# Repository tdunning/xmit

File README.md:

# XMIT - New tools for old jobs

This repository has design files and (soon) code for a direct synthesis digital 
mode transmitter optimized for use on amateur bands. It should work well up to 
2m. The novelty here relative to other systems like the [QDX](https://qrp-labs.com/qdx.html)
lies in a few areas:

a) the use of [74LVC2G157](https://www.ti.com/lit/ds/symlink/sn74lvc2g157.pdf) to generate differential drive for a differential
driver such as the [THS6232](https://www.ti.com/lit/ds/symlink/ths6232.pdf) which can
directly drive most balanced antennas without a balun at up to about 5W. This design
avoids the need for fancy gate drive or paralleling FETs in favor of SMT packaging everywhere. 

b) the use of SMT inductors and SMT analog switches such as the 
[74lvc2g53](https://www.ti.com/lit/ds/symlink/sn74lvc2g53.pdf) or 
[74lvc1g66](https://www.ti.com/lit/ds/symlink/sn74lvc1g66.pdf).
This change is not earth-shattering, but it allows a much tighter all-SMT design with as much as 80dB suppression of harmonics.
The high degree of suppression is achieved by using a filter tuned to put the response zeros directly on the harmonics
and careful filter layout to suppress parasitic coupling.

# Transmit filtering

The design of the transmit chain uses one of a number of filters to
reject harmonics of the main frequency. One of these filters is
selected using analog switches to suit the desire transmission
frequency. These filters are designed to have minimal attenuation in
each of several amateur bands. Since these bands are relatively
narrow, passband flatness is not a grave concern. The zeros of the
filters are positioned near the second or third harmonics of the
carrier to suppress these frequencies very strongly. Higher harmonics
have nearly 75dB of suppression.

The response curves for the filters designed so far are shown below.

[Filter response curves](images/filters.png)

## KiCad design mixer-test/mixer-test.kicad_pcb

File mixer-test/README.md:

# Mixer Comparisons

This directory contains design files for PC boards intended to help compare different kinds of mixers, particularly in the HF to VHF regime. 

## The basics

This board has inputs for RF, local oscillator and and baseband outputs (if available). The local oscillator is assumed to be at 3.3V logic levels and is locally buffered to get a differential drive. Test points are available for internal signals.

## The contestants

The mixers available include the LT5560 and Tayloe mixers constructed using SN74CBT3253DR (similar to the FST3253), SN74LVC1G3157, or 74LVC1G66 analog switch. In all cases it is assumed that the desired output is limited to <100kHz. There is no presumption about the frequency of the RF or LO inputs other than they should be near enough to produce a useful baseband output.

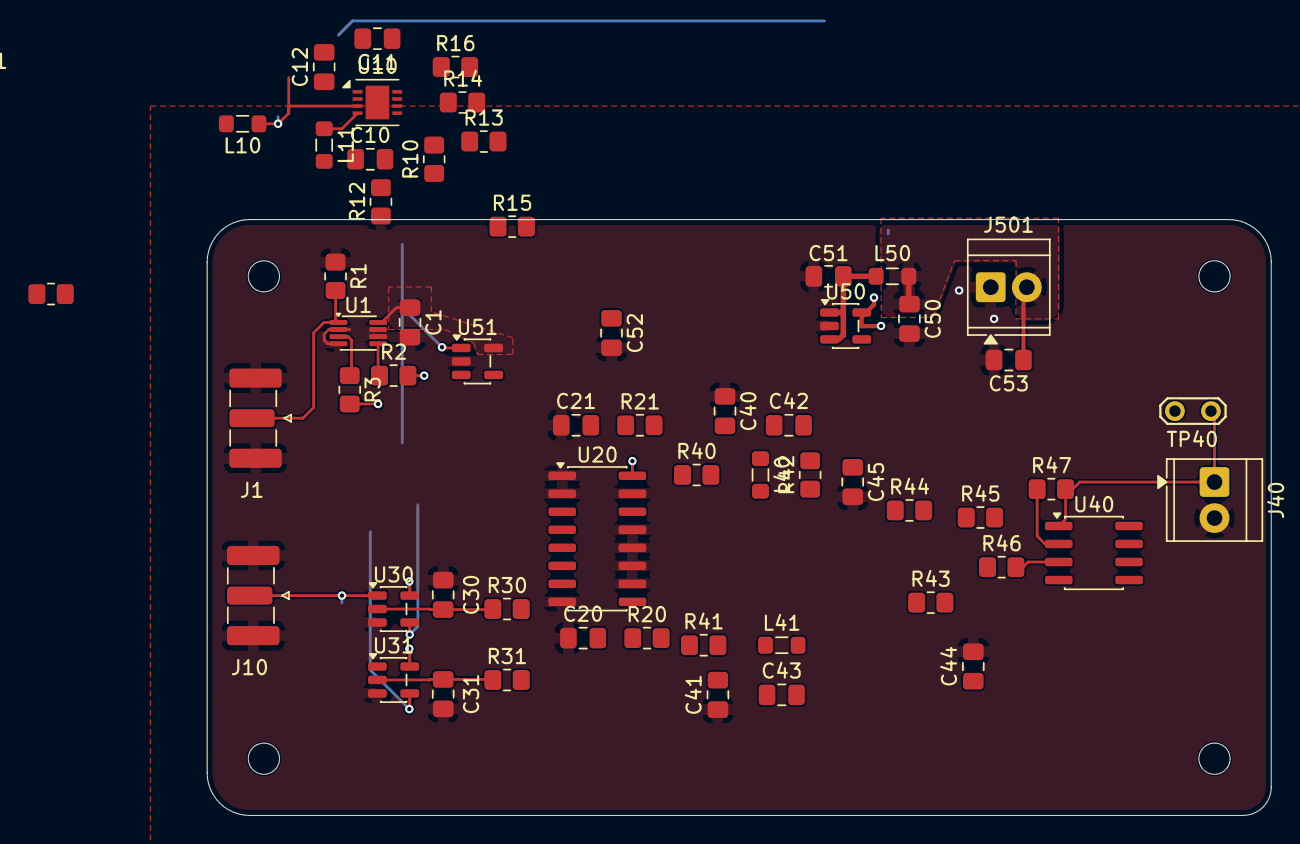
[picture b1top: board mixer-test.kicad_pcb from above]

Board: 4 copper layers, 75.0 x 42.0 mm, 62 parts (0 on the bottom side), 32 nets.

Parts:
C1, C12, C50, C51, C52, C53: 1µF; C_0805_2012Metric_Pad1.18x1.45mm_HandSolder
C10, C11: 220pF; C_0805_2012Metric_Pad1.18x1.45mm_HandSolder
C20, C21, C30, C31: 33pF; C_0805_2012Metric_Pad1.18x1.45mm_HandSolder
C40, C41, C44, C45: 1nF; C_0805_2012Metric_Pad1.18x1.45mm_HandSolder
C42, C43: 47pF; C_0805_2012Metric_Pad1.18x1.45mm_HandSolder
H501, H502, H503, H504: MountingHole_2.2mm_M2
J1, J10: SMA; SMA_Samtec_SMA-J-P-H-ST-EM1_EdgeMount
J40: Conn_01x02_Pin; TerminalBlock_TE_282834-2_1x02_P2.54mm_Horizontal
J501: TerminalBlock_TE_282834-2_1x02_P2.54mm_Horizontal
L10, L11: 100nH; L_0805_2012Metric_Pad1.05x1.20mm_HandSolder
L40, L41: 4.7µH; L_0805_2012Metric_Pad1.05x1.20mm_HandSolder
L50: 1 µH; L_0805_2012Metric_Pad1.05x1.20mm_HandSolder
R1, R10, R12: 100R; R_0805_2012Metric_Pad1.20x1.40mm_HandSolder
R2, R3, R11: 50R; R_0805_2012Metric_Pad1.20x1.40mm_HandSolder
R13, R14: 330R; R_0805_2012Metric_Pad1.20x1.40mm_HandSolder
R15, R16, R20, R21, R30, R31: 0R; R_0805_2012Metric_Pad1.20x1.40mm_HandSolder
R40, R41: 1k; R_0805_2012Metric_Pad1.20x1.40mm_HandSolder
R42, R43: 10R; R_0805_2012Metric_Pad1.20x1.40mm_HandSolder
R44, R45, R46, R47: 10k; R_0805_2012Metric_Pad1.20x1.40mm_HandSolder
TP40: Output; TestPoint_2Pads_Pitch2.54mm_Drill0.8mm
U1: 74LVC2G157; VSSOP-8_2.3x2mm_P0.5mm
U10: LT5560; DFN-8-1EP_3x3mm_P0.5mm_EP1.66x2.38mm
U20: SN74CBT3253; SOIC-16_3.9x9.9mm_P1.27mm
U30, U31: 74LVC1G66; SOT-23-5
U40: OPA2356AIDR; SOIC-8_3.9x4.9mm_P1.27mm
U50: TPS7A2042PDBVRG4; SOT-23-5
U51: TPS7A2033PDBVRG4; SOT-23-5

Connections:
GND: C1.2, C12.2, C20.1, C21.1, C30.1, C31.1, C40.1, C41.1, C44.2, C45.2, C50.2, C51.2, C52.2, C53.2, J1.2 (Ext), J10.2 (Ext), J40.2, J501.1, L10.2, L11.2, R1.1, R10.1, R11.1, R12.1, U1.2 (B), U1.4 (GND), U1.6 (~A/B), U1.7 (~G), U10.9 (PGND), U20.1 (1~OE), U20.2 (S1), U20.8 (GND), U20.10 (2B1), U20.11 (2B2), U20.12 (2B3), U20.13 (2B4), U20.15 (2~OE), U30.3 (GND), U31.3 (GND), U50.2 (GND), U51.2 (GND)
LO: C11.1, R2.2, R10.2, U20.14 (S0), U30.4
unnamed: C30.2, R30.1, U30.2
unnamed: C31.2, R31.1, U31.2
unnamed: C40.2, C42.1, L40.1, R40.2
unnamed: C41.2, C43.1, L41.1, R41.2
unnamed: C42.2, C45.1, R42.2, R44.1
unnamed: C43.2, C44.1, R43.2, R45.1
unnamed: J1.1 (In), R1.2, U1.1 (A)
unnamed: L40.2, R42.1
unnamed: L41.2, R43.1
unnamed: R2.1, U1.5 (Y)
unnamed: R3.1, U1.3 (~Y)
unnamed: L11.1, U10.4 (IN-)
unnamed: C10.2, U10.8 (LO+)
unnamed: C11.2, U10.1 (LO-)
unnamed: R13.2, R15.1, U10.6 (OUT+)
unnamed: R14.2, R16.1, U10.5 (OUT-)
unnamed: C20.2, R20.1, U20.6 (1B1)
unnamed: C21.2, R21.1, U20.5 (1B2)
unnamed: R44.2, R46.2, U40.3 (+)
unnamed: R45.2, R47.1, U40.2 (-)
unnamed: C51.1, L50.2, U50.1 (VIN), U50.3 (EN)
OUT+: R15.2, R20.2, R30.2, R41.1
OUT-: R16.2, R21.2, R31.2, R40.1
OUTPUT: J40.1, R47.2, TP40.1 (1_1), U40.1
RF: J10.1 (In), L10.1, R11.2, U10.3 (IN+), U20.7 (1A), U30.1, U31.1
VCC: C50.1, C53.1, J501.2, L50.1, U51.1 (VIN), U51.3 (EN)
V_amp: R13.1, R14.1
V_drive: C1.1, U1.8 (VCC), U51.5 (VOUT)
V_mix: C12.1, C52.1, U10.2 (EN), U10.7 (VCC), U20.16 (VCC), U30.5 (VCC), U31.5 (VCC), U50.5 (VOUT)
~LO: C10.1, R3.2, R12.2, U31.4

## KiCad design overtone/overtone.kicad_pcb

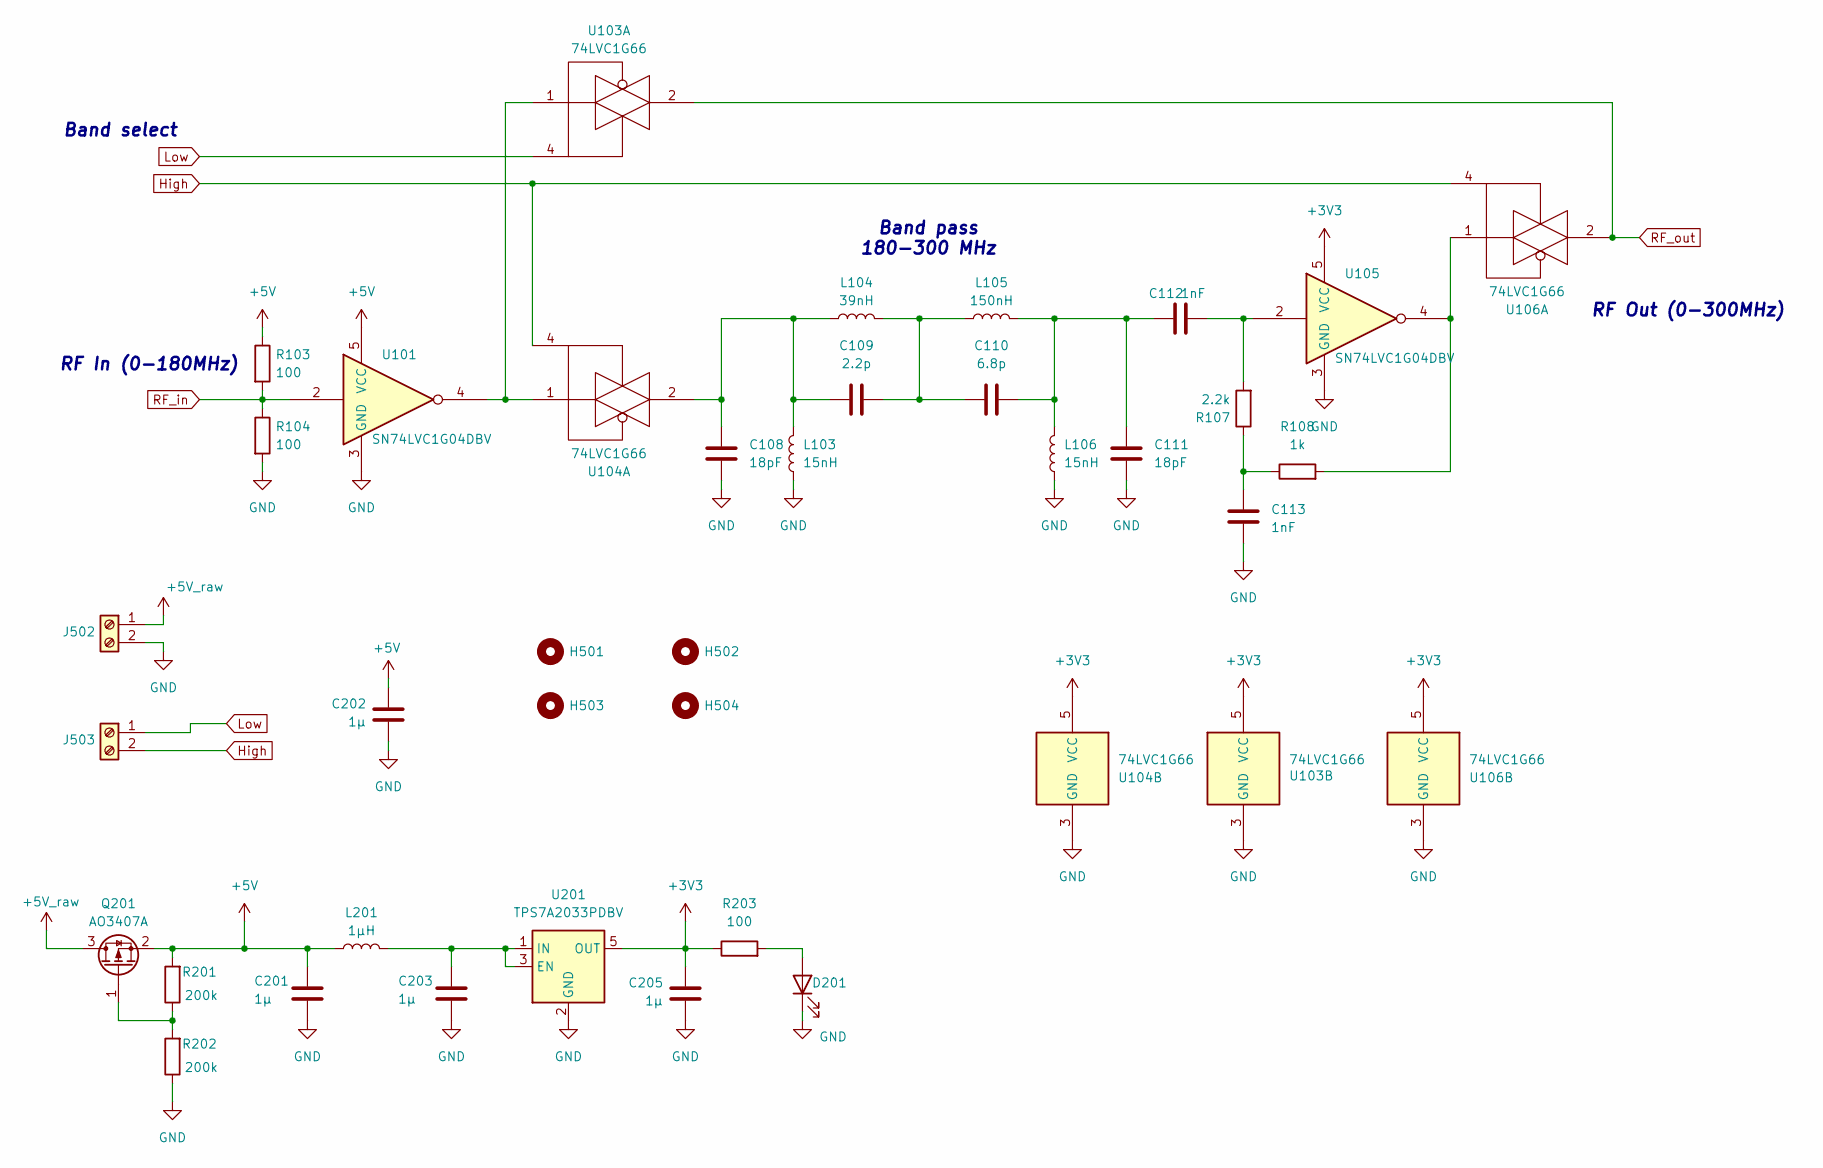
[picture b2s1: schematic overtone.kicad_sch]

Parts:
C108, C111: 18pF; C_0805_2012Metric_Pad1.18x1.45mm_HandSolder; LCSC Part # C519933
C109: 2.2p; C_0805_2012Metric_Pad1.18x1.45mm_HandSolder; LCSC Part # C519933
C110: 6.8p; C_0805_2012Metric_Pad1.18x1.45mm_HandSolder; LCSC Part # C76626
C112: 1nF; C_0805_2012Metric_Pad1.18x1.45mm_HandSolder
C113: 1nF; C_0805_2012Metric_Pad1.18x1.45mm_HandSolder; LCSC Part # C519933
C201, C202, C203, C205: 1µ; C_0805_2012Metric; LCSC Part # C76645
D201: LED; LED_0603_1608Metric; LCSC Part # C12065
H501, H502, H503, H504: MountingHole_2.2mm_M2
J502, J503: TerminalBlock_TE_282834-2_1x02_P2.54mm_Horizontal
L103, L106: 15nH; L_0805_2012Metric_Pad1.05x1.20mm_HandSolder; LCSC Part # C98996
L104: 39nH; L_0805_2012Metric_Pad1.05x1.20mm_HandSolder; LCSC Part # C98996
L105: 150nH; L_0805_2012Metric_Pad1.05x1.20mm_HandSolder; LCSC Part # C98996
L201: 1µH; L_0805_2012Metric_Pad1.05x1.20mm_HandSolder; LCSC Part # C19533
Q201: AO3407A; SOT-23; LCSC Part # C15155
R103: 100; R_0805_2012Metric_Pad1.20x1.40mm_HandSolder; LCSC Part # C114567
R104: 100; R_0805_2012Metric_Pad1.20x1.40mm_HandSolder; LCSC Part # C17378
R107: 2.2k; R_0805_2012Metric_Pad1.20x1.40mm_HandSolder; LCSC Part # C17378
R108: 1k; R_0805_2012Metric_Pad1.20x1.40mm_HandSolder
R201, R202: 200k; R_0805_2012Metric_Pad1.20x1.40mm_HandSolder; LCSC Part # C17539
R203: 100; R_0603_1608Metric; LCSC Part # C22775
U101, U105: SN74LVC1G04DBV; SOT-23-5; LCSC Part # C45367201
U103, U104, U106: 74LVC1G66; SOT-23-5; LCSC Part # C113518
U201: TPS7A2033PDBV; SOT-23-5; LCSC Part # C7827

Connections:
+3V3: C205.2, R203.1, U103.5 (VCC), U104.5 (VCC), U105.5 (VCC), U106.5 (VCC), U201.5 (OUT)
+5V: C201.2, C202.2, L201.1, Q201.2 (S), R103.1, R201.2, U101.5 (VCC)
+5V_raw: J502.1, Q201.3 (D)
GND: C108.1, C111.1, C113.1, C201.1, C202.1, C203.1, C205.1, D201.1 (K), J502.2, L103.1, L106.1, R104.2, R202.1, U101.3 (GND), U103.3 (GND), U104.3 (GND), U105.3 (GND), U106.3 (GND), U201.2 (GND); also elsewhere on the board
High: J503.2, U104.4, U106.4
Low: J503.1, U103.4
unnamed: C108.2, C109.1, L103.2, L104.1, U104.2
unnamed: C109.2, C110.1, L104.2, L105.1
unnamed: C110.2, C111.2, C112.1, L105.2, L106.2
unnamed: C112.2, R107.2, U105.2
unnamed: C113.2, R107.1, R108.1
unnamed: D201.2 (A), R203.2
unnamed: Q201.1 (G), R201.1, R202.2
unnamed: R108.2, U105.4, U106.1
unnamed: U101.4, U103.1, U104.1
unnamed: C203.2, L201.2, U201.1 (IN), U201.3 (EN)
RF_in: R103.2, R104.1, U101.2; also elsewhere on the board
RF_out: U103.2, U106.2

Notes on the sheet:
Band select
RF In (0-180MHz)
RF Out (0-300MHz)
Band pass 180-300 MHz

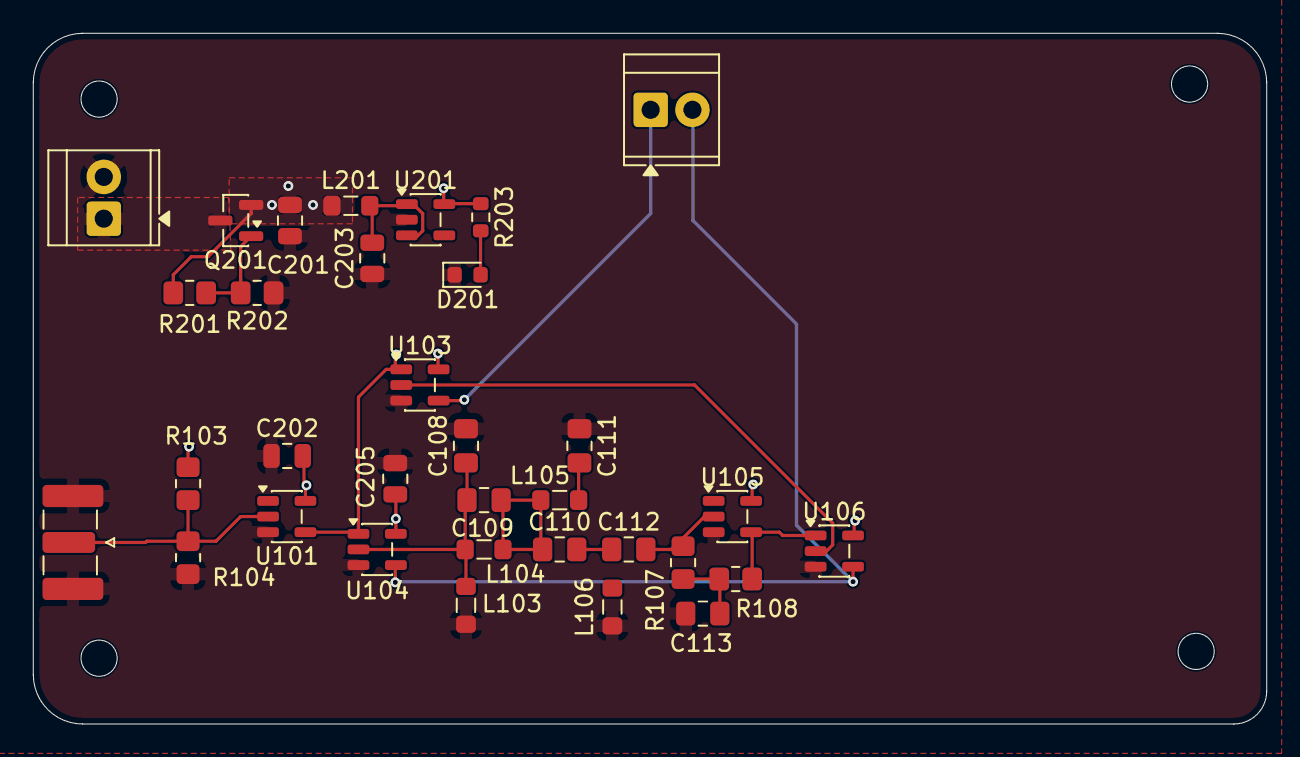
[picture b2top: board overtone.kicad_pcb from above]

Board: 4 copper layers, 75.0 x 42.0 mm, 37 parts (0 on the bottom side), 18 nets.

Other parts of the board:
J506: SMA_Samtec_SMA-J-P-H-ST-EM1_EdgeMount

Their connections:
GND: J506.2 (Ext); also elsewhere on the board
RF_in: J506.1 (In); also elsewhere on the board

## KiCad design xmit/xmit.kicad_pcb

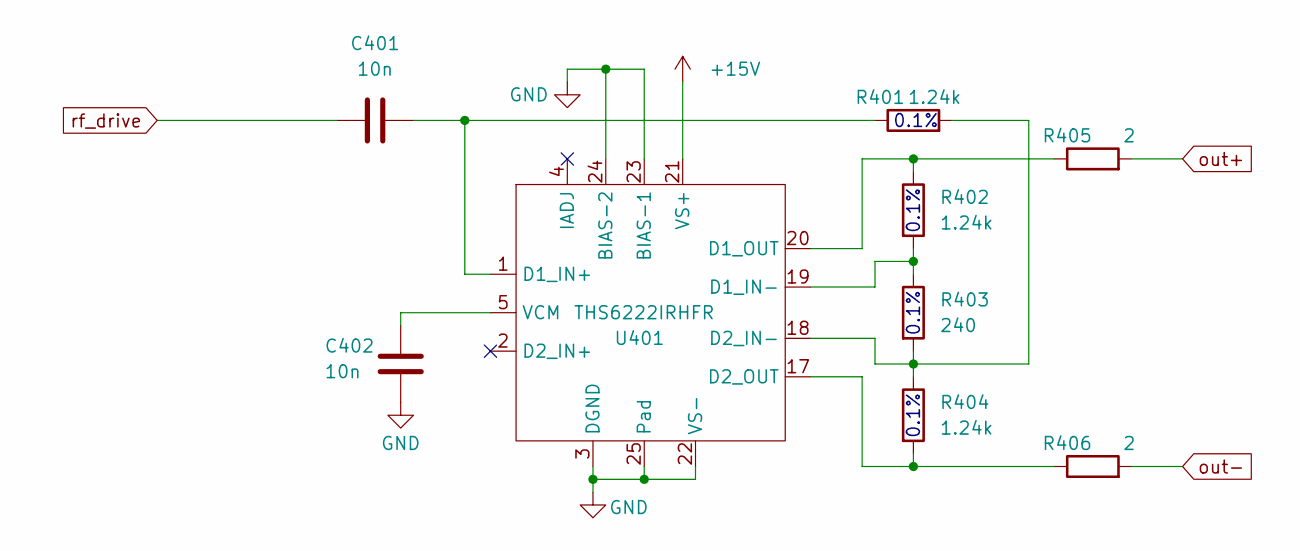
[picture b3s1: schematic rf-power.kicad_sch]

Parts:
C401, C402: 10n; C_0805_2012Metric_Pad1.18x1.45mm_HandSolder; LCSC Part # C76626
R401, R402, R404: 1.24k; R_0402_1005Metric; LCSC Part # C852604
R403: 240; R_0402_1005Metric; LCSC Part # C17572
R405, R406: 2; R_0805_2012Metric_Pad1.20x1.40mm_HandSolder; LCSC Part # C101983
U401: THS6222IRHFR; QFN-24-1EP_4x5mm_P0.5mm_EP2.65x3.65mm_ThermalVias; LCSC Part # C1855812

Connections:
+15V: U401.21 (VS+); also elsewhere on the board
GND: C402.1, U401.3 (DGND), U401.22 (VS-), U401.23 (BIAS-1), U401.24 (BIAS-2), U401.25 (Pad); also elsewhere on the board
unnamed: C401.2, R401.1, U401.1 (D1_IN+)
unnamed: R402.2, R403.1, U401.19 (D1_IN-)
unnamed: R402.1, R405.1, U401.20 (D1_OUT)
unnamed: R401.2, R403.2, R404.1, U401.18 (D2_IN-)
unnamed: R404.2, R406.1, U401.17 (D2_OUT)
unnamed: C402.2, U401.5 (VCM)
out+: R405.2; also elsewhere on the board
out-: R406.2; also elsewhere on the board
rf_drive: C401.1; also elsewhere on the board

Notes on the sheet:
0.1%

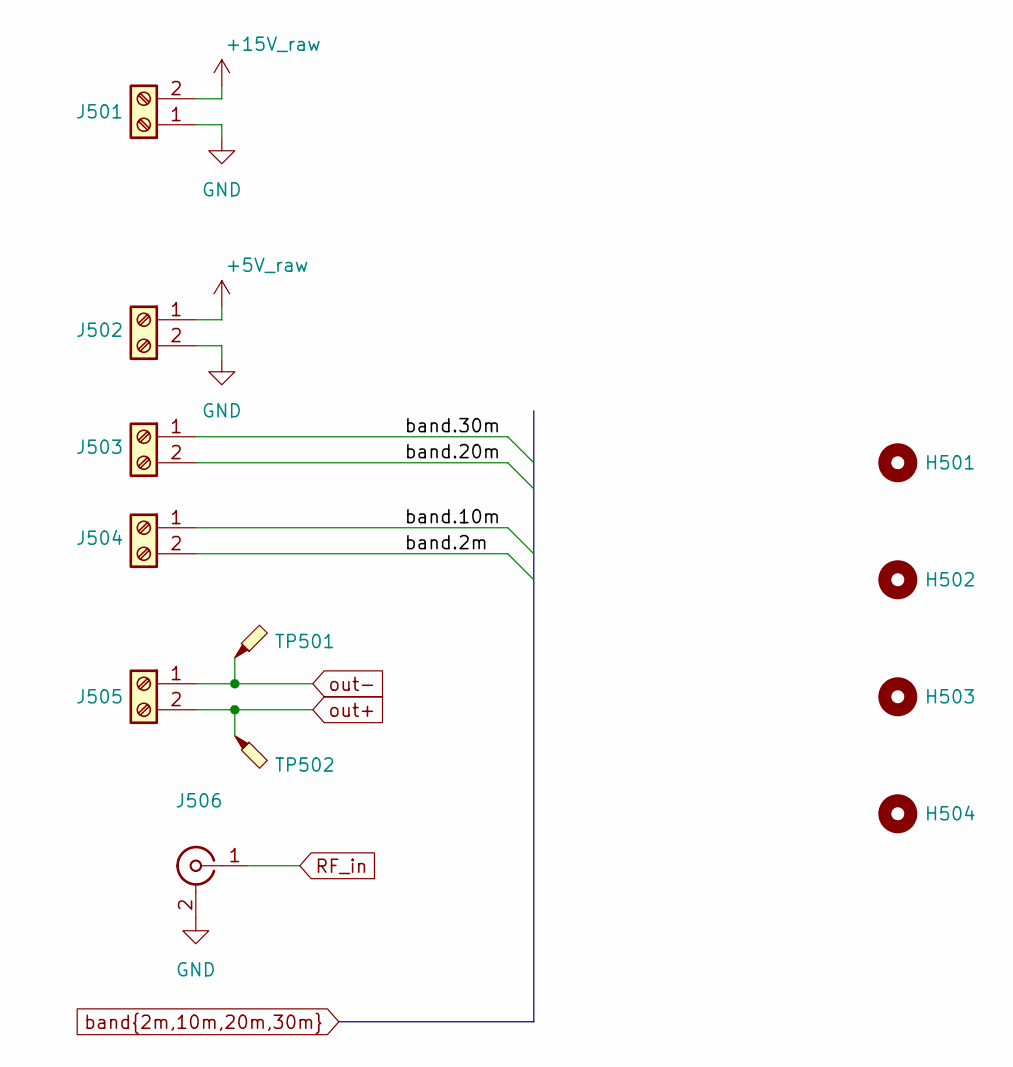
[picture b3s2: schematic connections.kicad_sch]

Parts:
H501, H502, H503, H504: MountingHole_2.2mm_M2
J501, J502, J503, J504, J505: TerminalBlock_TE_282834-2_1x02_P2.54mm_Horizontal
J506: SMA_Samtec_SMA-J-P-H-ST-EM1_EdgeMount; LCSC Part # C49118400
TP501: TestPoint_2Pads_Pitch2.54mm_Drill0.8mm; LCSC Part # C45367201
TP502: TestPoint_2Pads_Pitch2.54mm_Drill0.8mm; LCSC Part # C113518

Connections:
+5V_raw: J502.1; also elsewhere on the board
+15V_raw: J501.2; also elsewhere on the board
GND: J501.1, J502.2, J506.2 (Ext); also elsewhere on the board
RF_in: J506.1 (In); also elsewhere on the board
band.2m: J504.2; also elsewhere on the board
band.10m: J504.1; also elsewhere on the board
band.20m: J503.2; also elsewhere on the board
band.30m: J503.1; also elsewhere on the board
out+: J505.2, TP502.1 (1_1); also elsewhere on the board
out-: J505.1, TP501.1 (1_1); also elsewhere on the board

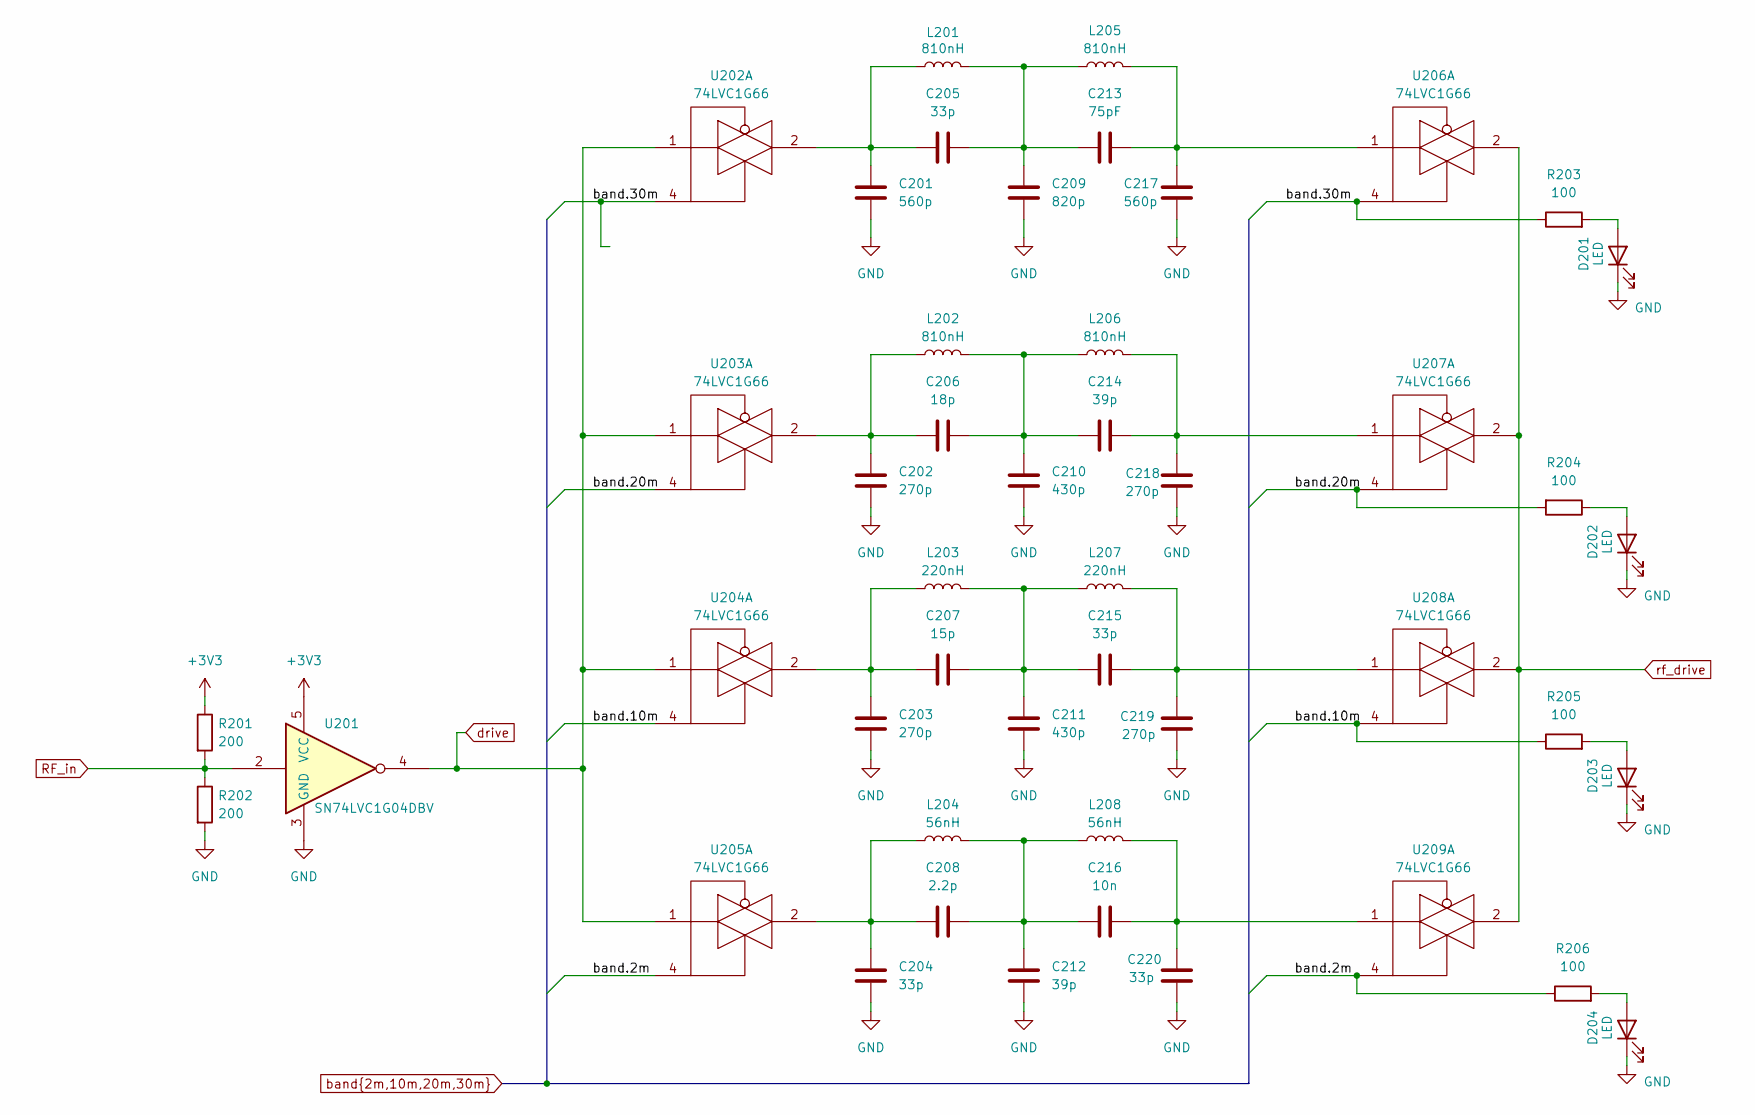
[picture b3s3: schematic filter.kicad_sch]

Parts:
C201: 560p; C_0805_2012Metric_Pad1.18x1.45mm_HandSolder; LCSC Part # C107119
C202: 270p; C_0805_2012Metric_Pad1.18x1.45mm_HandSolder; LCSC Part # C107106
C203: 270p; C_0805_2012Metric_Pad1.18x1.45mm_HandSolder; LCSC Part # C113828
C204: 33p; C_0805_2012Metric_Pad1.18x1.45mm_HandSolder; LCSC Part # C107115
C205, C215, C220: 33p; C_0805_2012Metric_Pad1.18x1.45mm_HandSolder; LCSC Part # C85970
C206: 18p; C_0805_2012Metric_Pad1.18x1.45mm_HandSolder; LCSC Part # C113825
C207: 15p; C_0805_2012Metric_Pad1.18x1.45mm_HandSolder; LCSC Part # C107110
C208: 2.2p; C_0805_2012Metric_Pad1.18x1.45mm_HandSolder; LCSC Part # C519933
C209: 820p; C_0805_2012Metric_Pad1.18x1.45mm_HandSolder; LCSC Part # C309484
C210: 430p; C_0805_2012Metric_Pad1.18x1.45mm_HandSolder; LCSC Part # C520006
C211: 430p; C_0805_2012Metric_Pad1.18x1.45mm_HandSolder; LCSC Part # C126556
C212: 39p; C_0805_2012Metric_Pad1.18x1.45mm_HandSolder; LCSC Part # C107117
C213: 75pF; C_0805_2012Metric_Pad1.18x1.45mm_HandSolder; LCSC Part # C113832
C214: 39p; C_0805_2012Metric_Pad1.18x1.45mm_HandSolder; LCSC Part # C76645
C216: 10n; C_0805_2012Metric_Pad1.18x1.45mm_HandSolder; LCSC Part # C76626
C217: 560p; C_0805_2012Metric_Pad1.18x1.45mm_HandSolder; LCSC Part # C97881
C218, C219: 270p; C_0805_2012Metric_Pad1.18x1.45mm_HandSolder; LCSC Part # C2986280
D201, D202, D203, D204: LED; LED_0603_1608Metric; LCSC Part # C12065
L201: 810nH; L_0805_2012Metric_Pad1.05x1.20mm_HandSolder; LCSC Part # C139231
L202, L205, L206: 810nH; L_0805_2012Metric_Pad1.05x1.20mm_HandSolder; LCSC Part # C98996
L203, L207: 220nH; L_0805_2012Metric_Pad1.05x1.20mm_HandSolder; LCSC Part # C108960
L204, L208: 56nH; L_0805_2012Metric_Pad1.05x1.20mm_HandSolder; LCSC Part # C98996
R201: 200; R_0805_2012Metric_Pad1.20x1.40mm_HandSolder; LCSC Part # C114567
R202: 200; R_0805_2012Metric_Pad1.20x1.40mm_HandSolder; LCSC Part # C17378
R203, R204, R205, R206: 100; R_0603_1608Metric; LCSC Part # C22775
U201: SN74LVC1G04DBV; SOT-23-5; LCSC Part # C45367201
U202, U203, U204, U205, U206, U207, U208, U209: 74LVC1G66; SOT-23-5; LCSC Part # C113518

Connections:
+3V3: R201.1, U201.5 (VCC); also elsewhere on the board
GND: C201.2, C202.2, C203.2, C204.2, C209.2, C210.2, C211.2, C212.2, C217.2, C218.2, C219.2, C220.2, D201.1 (K), D202.1 (K), D203.1 (K), D204.1 (K), R202.2, U201.3 (GND); also elsewhere on the board
unnamed: C201.1, C205.1, L201.1, U202.2
unnamed: C202.1, C206.1, L202.1, U203.2
unnamed: C203.1, C207.1, L203.1, U204.2
unnamed: C204.1, C208.1, L204.1, U205.2
unnamed: C205.2, C209.1, C213.1, L201.2, L205.1
unnamed: C206.2, C210.1, C214.1, L202.2, L206.1
unnamed: C207.2, C211.1, C215.1, L203.2, L207.1
unnamed: C208.2, C212.1, C216.1, L204.2, L208.1
unnamed: C213.2, C217.1, L205.2, U206.1
unnamed: C214.2, C218.1, L206.2, U207.1
unnamed: C215.2, C219.1, L207.2, U208.1
unnamed: C216.2, C220.1, L208.2, U209.1
unnamed: D201.2 (A), R203.2
unnamed: D202.2 (A), R204.1
unnamed: D203.2 (A), R205.2
unnamed: D204.2 (A), R206.2
RF_in: R201.2, R202.1, U201.2; also elsewhere on the board
band.2m: R206.1, U205.4, U209.4; also elsewhere on the board
band.10m: R205.1, U204.4, U208.4; also elsewhere on the board
band.20m: R204.2, U203.4, U207.4; also elsewhere on the board
band.30m: R203.1, U202.4, U206.4; also elsewhere on the board
drive: U201.4, U202.1, U203.1, U204.1, U205.1
rf_drive: U206.2, U207.2, U208.2, U209.2; also elsewhere on the board

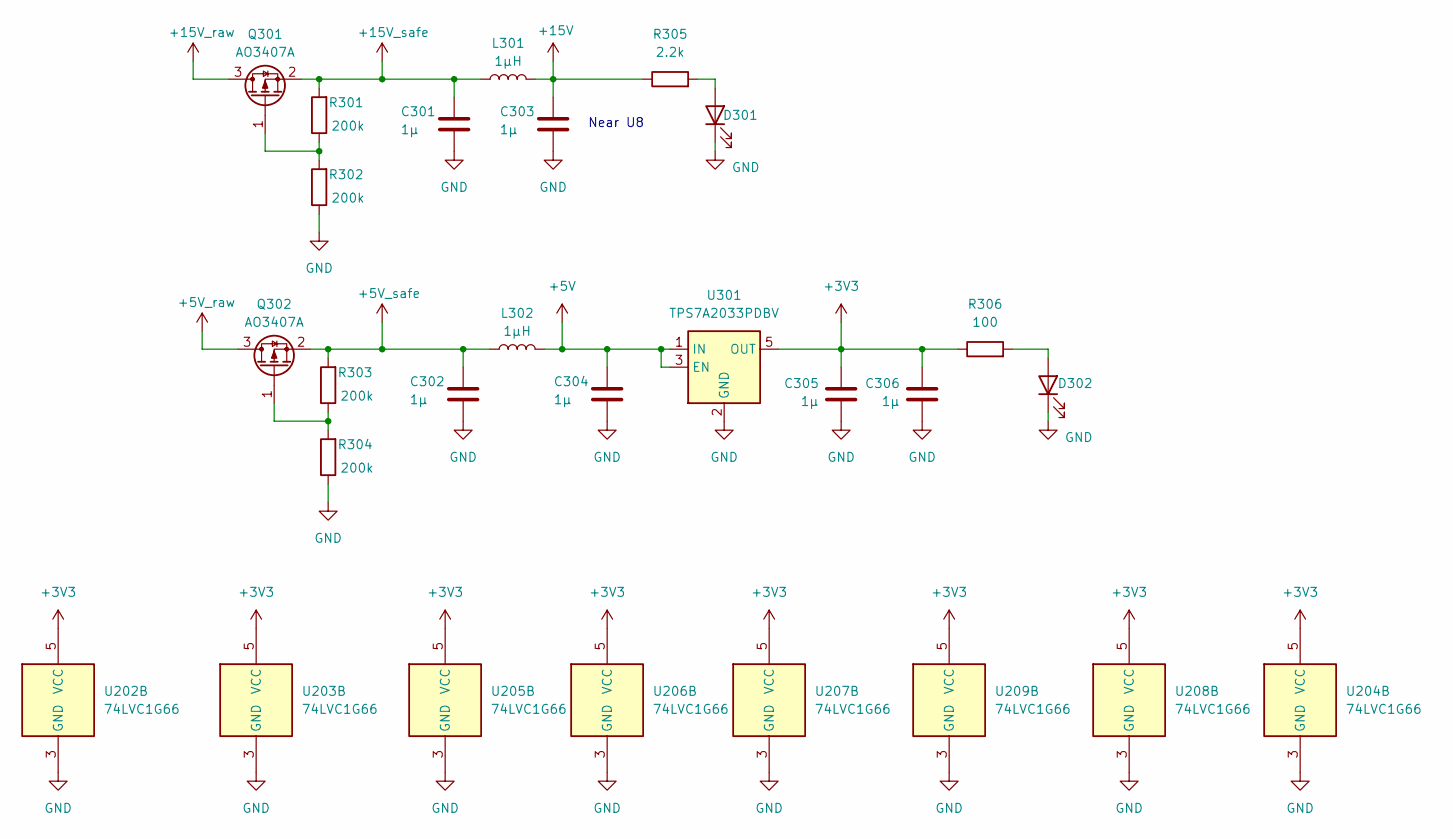
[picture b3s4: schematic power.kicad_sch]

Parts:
C301, C302, C303, C304, C305, C306: 1µ; C_0805_2012Metric; LCSC Part # C76645
D301, D302: LED; LED_0603_1608Metric; LCSC Part # C12065
L301, L302: 1µH; L_0805_2012Metric_Pad1.05x1.20mm_HandSolder; LCSC Part # C19533
Q301, Q302: AO3407A; SOT-23; LCSC Part # C15155
R301, R302, R303, R304: 200k; R_0805_2012Metric_Pad1.20x1.40mm_HandSolder; LCSC Part # C17539
R305: 2.2k; R_0603_1608Metric; LCSC Part # C113303
R306: 100; R_0603_1608Metric; LCSC Part # C22775
U202, U203, U204, U205, U206, U207, U208, U209: 74LVC1G66; SOT-23-5; LCSC Part # C113518
U301: TPS7A2033PDBV; SOT-23-5; LCSC Part # C7827

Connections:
+3V3: C305.2, C306.2, R306.1, U202.5 (VCC), U203.5 (VCC), U204.5 (VCC), U205.5 (VCC), U206.5 (VCC), U207.5 (VCC), U208.5 (VCC), U209.5 (VCC), U301.5 (OUT); also elsewhere on the board
+5V: C304.2, L302.2, U301.1 (IN), U301.3 (EN)
+5V_raw: Q302.3 (D); also elsewhere on the board
+5V_safe: C302.2, L302.1, Q302.2 (S), R303.2
+15V: C303.2, L301.2, R305.1; also elsewhere on the board
+15V_raw: Q301.3 (D); also elsewhere on the board
+15V_safe: C301.2, L301.1, Q301.2 (S), R301.2
GND: C301.1, C302.1, C303.1, C304.1, C305.1, C306.1, D301.1 (K), D302.1 (K), R302.1, R304.1, U202.3 (GND), U203.3 (GND), U204.3 (GND), U205.3 (GND), U206.3 (GND), U207.3 (GND), U208.3 (GND), U209.3 (GND), U301.2 (GND); also elsewhere on the board
unnamed: D301.2 (A), R305.2
unnamed: D302.2 (A), R306.2
unnamed: Q301.1 (G), R301.1, R302.2
unnamed: Q302.1 (G), R303.1, R304.2

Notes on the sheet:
Near U8

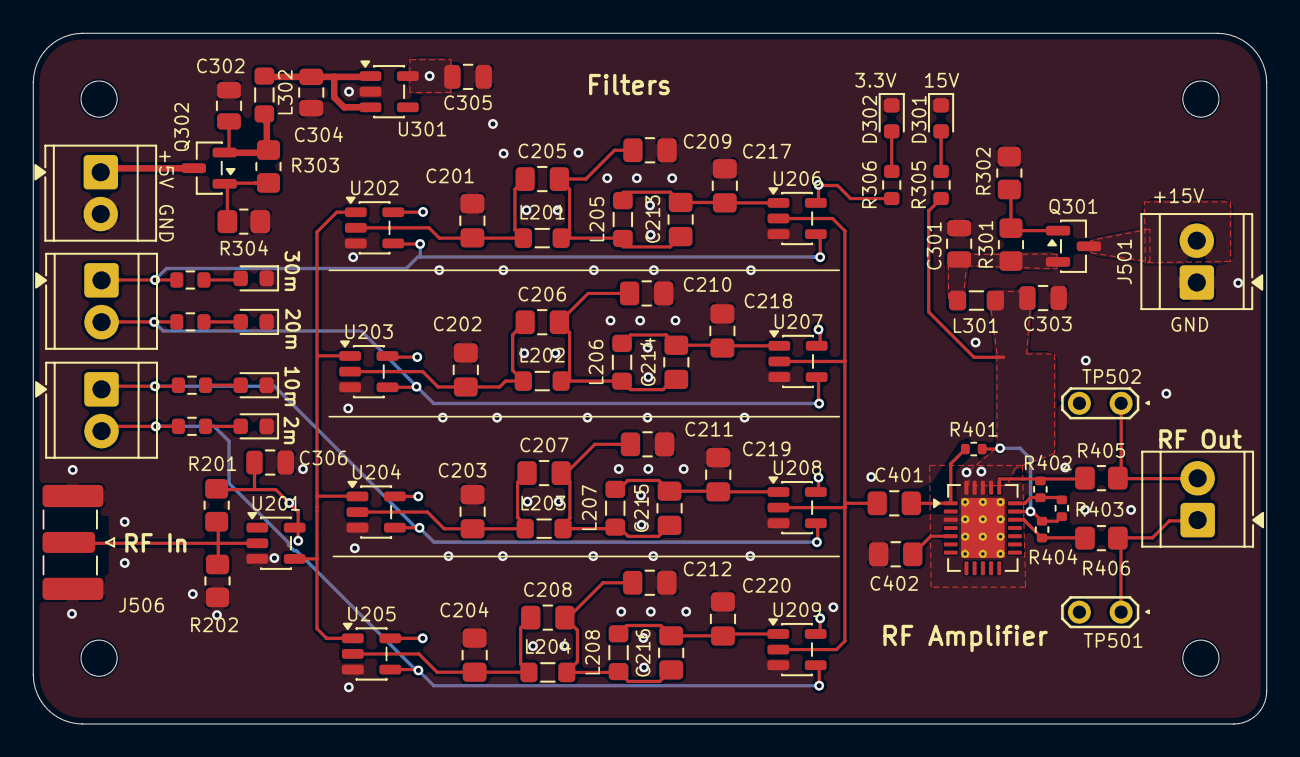
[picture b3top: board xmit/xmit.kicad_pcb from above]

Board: 4 copper layers, 75.0 x 42.0 mm, 87 parts (0 on the bottom side), 43 nets.

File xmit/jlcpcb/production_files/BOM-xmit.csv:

1.24k,"R401,R402,R404",R_0402_1005Metric,C852604,3
100,R306,R_0603_1608Metric,C22775,1
10n,"C216,C401,C402",C_0805_2012Metric_Pad1.18x1.45mm_HandSolder,C76626,3
15p,C207,C_0805_2012Metric_Pad1.18x1.45mm_HandSolder,C107110,1
18p,C206,C_0805_2012Metric_Pad1.18x1.45mm_HandSolder,C113825,1
1µ,"C301,C302,C303,C304,C305,C306",C_0805_2012Metric,C76645,6
1µH,"L301,L302",L_0805_2012Metric_Pad1.05x1.20mm_HandSolder,C19533,2
2.2k,R305,R_0603_1608Metric,C113303,1
200,"R201,R202",R_0805_2012Metric_Pad1.20x1.40mm_HandSolder,C114567,2
220nH,"L203,L207",L_0805_2012Metric_Pad1.05x1.20mm_HandSolder,C108960,2
240,R403,R_0402_1005Metric,C102913,1
270p,"C202,C203,C218,C219",C_0805_2012Metric_Pad1.18x1.45mm_HandSolder,C113828,4
33p,"C204,C205,C215,C220",C_0805_2012Metric_Pad1.18x1.45mm_HandSolder,C107115,4
39p,"C212,C214",C_0805_2012Metric_Pad1.18x1.45mm_HandSolder,C107117,2
430p,"C210,C211",C_0805_2012Metric_Pad1.18x1.45mm_HandSolder,C520006,2
560p,"C201,C217",C_0805_2012Metric_Pad1.18x1.45mm_HandSolder,C107119,2
56nH,"L204,L208",L_0805_2012Metric_Pad1.05x1.20mm_HandSolder,C98996,2
74LVC1G66,"U202,U203,U204,U205,U206,U207,U208,U209",SOT-23-5,C133643,8
75pF,C213,C_0805_2012Metric_Pad1.18x1.45mm_HandSolder,C113832,1
810nH,"L201,L202,L205,L206",L_0805_2012Metric_Pad1.05x1.20mm_HandSolder,C139231,4
820p,C209,C_0805_2012Metric_Pad1.18x1.45mm_HandSolder,C309484,1
AO3407A,"Q301,Q302",SOT-23,C15155,2

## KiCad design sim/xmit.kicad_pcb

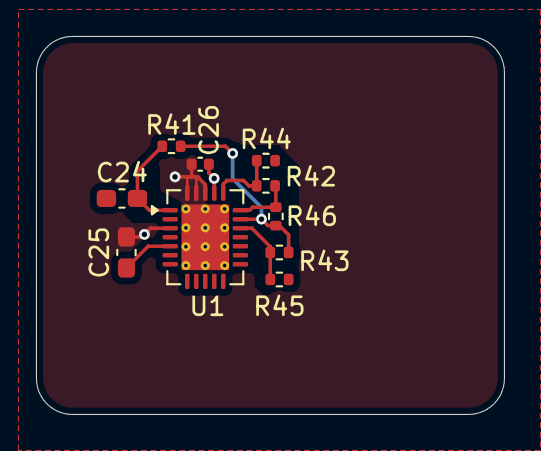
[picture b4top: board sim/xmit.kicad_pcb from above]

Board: 4 copper layers, 26.0 x 21.0 mm, 10 parts (0 on the bottom side), 8 nets.

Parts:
C24, C25: 100n; C_0603_1608Metric_Pad1.08x0.95mm_HandSolder
C26: 1u; C_0402_1005Metric
R41, R42, R43: 1.24k; R_0402_1005Metric
R44, R45: 2.5; R_0402_1005Metric
R46: 237; R_0402_1005Metric
U1: QFN-24-1EP_4x5mm_P0.5mm_EP2.65x3.65mm_ThermalVias

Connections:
+12V: C26.2, U1.21 (VS+)
GND: C25.1, C26.1, U1.3 (DGND), U1.22 (VS-), U1.23 (BIAS-1), U1.24 (BIAS-2), U1.25 (Pad)
unnamed: R41.2, R43.1, R46.2, U1.18 (D2_IN-)
unnamed: C24.2, R41.1, U1.1 (D1_IN+)
unnamed: R42.2, R46.1, U1.19 (D1_IN-)
unnamed: R42.1, R44.1, U1.20 (D1_OUT)
unnamed: R43.2, R45.1, U1.17 (D2_OUT)
unnamed: C25.2, U1.5 (VCM)

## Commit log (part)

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2026-06-05 First round WIP on the filters and amplifier
2026-06-06 Fix typo
2026-06-15 WIP commit, but the circuit is nearly done and PCB is beginning for form.
2026-06-15 Cleanups
2026-06-15 More realistic simulations
2026-06-24 Updated filters and improved amp
2026-06-24 added filter responses
2026-06-29 Another WIP on transmitter layout. Should be pretty close.
